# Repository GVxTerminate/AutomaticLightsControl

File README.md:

# AutomaticLightsControl
The code in this repository would be used on the construction of an automated lights control circuit board project based on Microchip's pic18f micro-controllers

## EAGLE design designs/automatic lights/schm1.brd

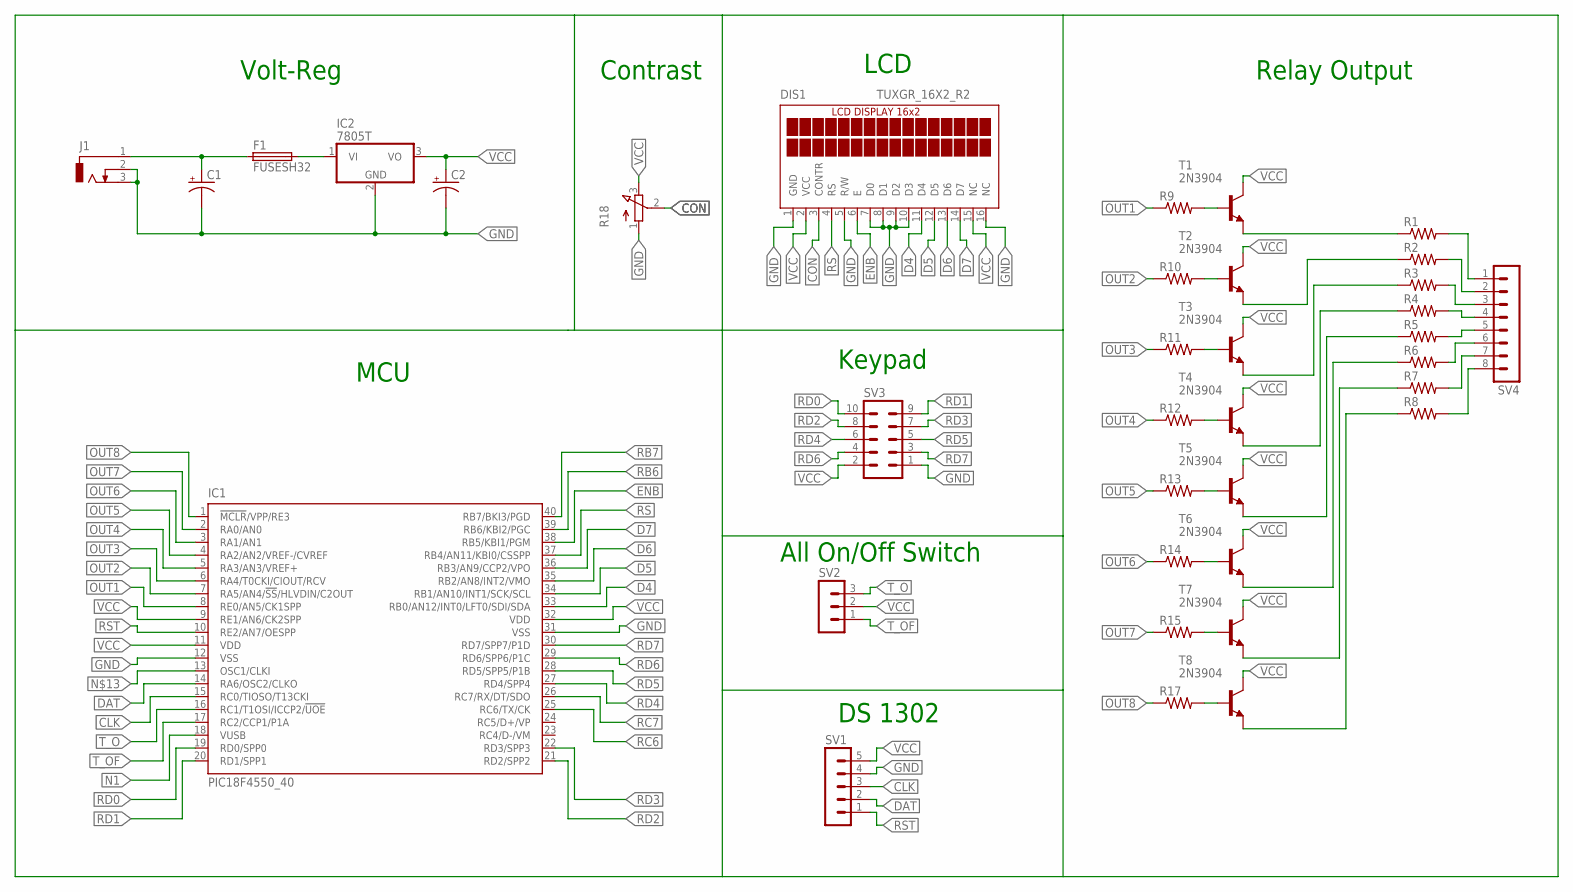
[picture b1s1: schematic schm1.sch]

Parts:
C1, C2: CPOL-USE5-10.5; E5-10,5
DIS1: TUXGR_16X2_R2
F1: FUSESH32; SH32
IC1: PIC18F4550_40; DIL40
IC2: 7805T; TO220H
J1: DCJ0303
R1, R2, R3, R4, R5, R6, R7, R8, R9, R10, R11, R12, R13, R14, R15, R17: R-US_0207/7; 0207/7
R18: 3RP/1610N
SV1: MA05-1
SV2: MA03-1
SV3: MA05-2
SV4: MA08-1
T1, T2, T3, T4, T5, T6, T7, T8: 2N3904; TO92

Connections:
CLK: IC1.15 (RC0/TIOSO/T13CKI), SV1.3
CON: DIS1.3 (CONTR), R18.2 (S)
D4: DIS1.11 (D4), IC1.33 (RB0/AN12/INT0/LFT0/SDI/SDA)
D5: DIS1.12 (D5), IC1.34 (RB1/AN10/INT1/SCK/SCL)
D6: DIS1.13 (D6), IC1.35 (RB2/AN8/INT2/VMO)
D7: DIS1.14 (D7), IC1.36 (RB3/AN9/CCP2/VPO)
DAT: IC1.14 (RA6/OSC2/CLKO), SV1.2
ENB: DIS1.6 (E), IC1.38 (RB5/KBI1/PGM)
GND: C1.-, C2.-, DIS1.1 (GND), DIS1.5 (R/W), DIS1.7 (D0), DIS1.8 (D1), DIS1.9 (D2), DIS1.10 (D3), DIS1.16 (NC), IC1.12 (VSS), IC1.31 (VSS), IC2.2 (GND), J1.2, J1.3, R18.1 (A), SV1.4, SV3.1
N1: IC1.18 (VUSB)
unnamed: C1.+, F1.1A (1), J1.1
unnamed: F1.2A (2), IC2.1 (VI)
unnamed: R1.2, SV4.1
unnamed: R2.2, SV4.2
unnamed: R3.2, SV4.3
unnamed: R4.2, SV4.4
unnamed: R5.2, SV4.5
unnamed: R6.2, SV4.6
unnamed: R7.2, SV4.7
unnamed: R8.2, SV4.8
unnamed: R1.1, T1.3 (E)
unnamed: R2.1, T2.3 (E)
unnamed: R3.1, T3.3 (E)
unnamed: R4.1, T4.3 (E)
unnamed: R5.1, T5.3 (E)
unnamed: R6.1, T6.3 (E)
unnamed: R9.2, T1.2 (B)
unnamed: R10.2, T2.2 (B)
unnamed: R11.2, T3.2 (B)
unnamed: R12.2, T4.2 (B)
unnamed: R13.2, T5.2 (B)
unnamed: R14.2, T6.2 (B)
unnamed: R15.2, T7.2 (B)
unnamed: R17.2, T8.2 (B)
unnamed: R7.1, T7.3 (E)
unnamed: R8.1, T8.3 (E)
OUT1: IC1.8 (RE0/AN5/CK1SPP), R9.1
OUT2: IC1.7 (RA5/AN4/!SS!/HLVDIN/C2OUT), R10.1
OUT3: IC1.6 (RA4/T0CKI/CIOUT/RCV), R11.1
OUT4: IC1.5 (RA3/AN3/VREF+), R12.1
OUT5: IC1.4 (RA2/AN2/VREF-/CVREF), R13.1
OUT6: IC1.3 (RA1/AN1), R14.1
OUT7: IC1.2 (RA0/AN0), R15.1
OUT8: IC1.1 (!MCLR!/VPP/RE3), R17.1
RB6: IC1.39 (RB6/KBI2/PGC)
RB7: IC1.40 (RB7/BKI3/PGD)
RC6: IC1.25 (RC6/TX/CK)
RC7: IC1.26 (RC7/RX/DT/SDO)
RD0: IC1.19 (RD0/SPP0), SV3.10
RD1: IC1.20 (RD1/SPP1), SV3.9
RD2: IC1.21 (RD2/SPP2), SV3.8
RD3: IC1.22 (RD3/SPP3), SV3.7
RD4: IC1.27 (RD4/SPP4), SV3.6
RD5: IC1.28 (RD5/SPP5/P1B), SV3.5
RD6: IC1.29 (RD6/SPP6/P1C), SV3.4
RD7: IC1.30 (RD7/SPP7/P1D), SV3.3
RS: DIS1.4 (RS), IC1.37 (RB4/AN11/KBI0/CSSPP)
RST: IC1.10 (RE2/AN7/OESPP), SV1.1
T_O: IC1.16 (RC1/T1OSI/ICCP2/!UOE), SV2.3
T_OF: IC1.17 (RC2/CCP1/P1A), SV2.1
VCC: C2.+, DIS1.2 (VCC), DIS1.15 (NC), IC1.9 (RE1/AN6/CK2SPP), IC1.11 (VDD), IC1.32 (VDD), IC2.3 (VO), R18.3 (E), SV1.5, SV2.2, SV3.2, T1.1 (C), T2.1 (C), T3.1 (C), T4.1 (C), T5.1 (C), T6.1 (C), T7.1 (C), T8.1 (C)

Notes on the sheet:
Volt-Reg
MCU
Contrast
LCD
DS 1302
All On/Off Switch
Keypad
Relay Output

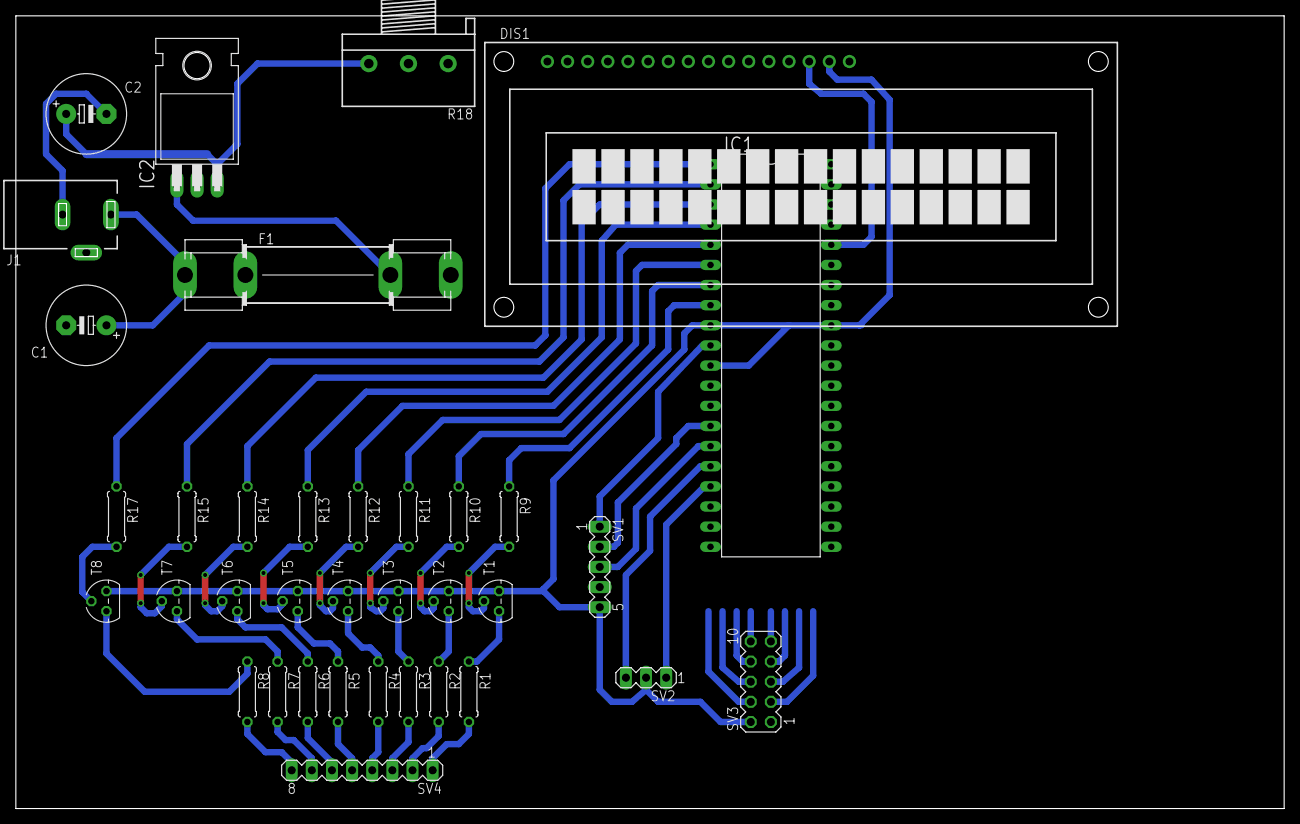
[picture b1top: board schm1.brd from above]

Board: 2 copper layers, 160.0 x 100.0 mm, 36 parts (0 on the bottom side), 56 nets.

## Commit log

2017-02-17 first test commit
2017-02-20 Create Log
2017-02-22 Create schedule
2017-02-22 Create fd
2017-02-22 Create df
2017-02-22 Create hkj
2017-02-26 Update Log
2017-03-31 Cambios en tarjeta PCB
